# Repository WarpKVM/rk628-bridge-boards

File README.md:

# RK628H HDMI to MIPI CSI-2 bridge boards

Three small boards that turn an HDMI source into a MIPI CSI-2 camera stream,
built around the Rockchip RK628H. We designed them while building
[WarpKVM](https://warpkvm.com), used them to write and measure our capture
pipeline, and they are released here as open hardware so anyone can build on
them.

| | [`rk628-22p`](rk628-22p/) | [`rk628-30p`](rk628-30p/) | [`rk628-2x22p`](rk628-2x22p/) |
|---|---|---|---|
| Host connector | 22-pin FPC, 0.5 mm | 30-pin FPC, 0.5 mm | Two 22-pin FPCs, 0.5 mm |
| CSI-2 link | 4 lanes | 4 lanes | 2 x 4 lanes |
| Best mode | 4K30, 1080p120 | 4K30, 1080p120 | 4K60 (captured on the DIY shield) |
| Audio | I2S header | On-board DAC, 3.5 mm jack | I2S header |
| Size | 45 x 30 mm | 46.25 x 30 mm | 49 x 32.5 mm |
| Tested on | Luckfox Aura (RV1126B), Raspberry Pi CM4, Pi 4B lane count | Firefly ROC-RK3576-PC | Luckfox Aura, via the same circuit on our DIY shield |
| Install | One boot image (Aura) or one script that builds the driver (Pi) | Works on the factory image; one script for the patched kernel | One boot image |
| Status | Built and tested | Built and tested | Not yet fabricated |

The numbers on these pages were measured on real hardware, with the RK628H.
The RK628D also works on the single-link boards and is probably the better pick
for them; each board's README has the details.

## What is in each board folder

- `schematic/`: the schematic as a PDF
- `cad/`: the Fusion archive, plus EAGLE `.sch` and `.brd` files that KiCad can import
- `fab/`: gerbers, drill file, JLCPCB BOM and pick-and-place, and fab notes
  (stackup, impedance, finish)
- `images/`: photos, dimensions, a connection diagram and one image per layer

Host support (drivers, device trees, installers and EDIDs) is in [`hosts/`](hosts/).

## Why these boards

- **Up to 4K30 or 1080p120 on one 4-lane link**, and 4K60 over two
- **Custom EDIDs that apply live**, with no cable replug
- **HDMI audio**, over I2S to the host or to an on-board DAC
- **Automatic recovery** from the bridge lockup a hot HDMI replug can cause

The last three need the driver fixes in [`hosts/`](hosts/). Rockchip's stock
driver drops hot plug after an EDID write, never advertises audio, and caps the
lane rate on chips that do not need it. Each fix is described there.

## Getting started

1. Pick the board that matches your host's camera connector.
2. Start from the host's stock image: Firefly's Ubuntu, Luckfox's Debian or
   Raspberry Pi OS.
3. Connect the bridge with a 0.5 mm pitch FPC cable before powering on.
4. Run the installer for your host from the board's README, then
   `rk628-check.sh`, which finds the bridge, shows what the source is sending
   and captures a few hundred frames.

## Libraries

The Fusion libraries these boards use, with JLCPCB part numbers, schematic
frames and power symbols, are in
[groundplane-studio/fusion-libraries](https://github.com/groundplane-studio/fusion-libraries).

## Disclaimer

These boards and drivers are provided as is, with no warranty of any kind. They are
reference designs we've tested on the hosts listed above, not certified products.
Building, modifying or using them is at your own risk: check the design against your
own requirements, and we're not liable for damage to your hardware, your source devices
or anything else. The full terms are in the license files (CERN-OHL-S-2.0 for hardware,
GPL-2.0 for software).

## Licenses

- Hardware (schematics, layout, gerbers): CERN-OHL-S-2.0, see `LICENSE-HARDWARE`
- Software (kernel patches, drivers, device trees, scripts): GPL-2.0, see
  `LICENSE-SOFTWARE`, matching the Rockchip BSP driver they modify

Build, change and sell these boards under those licenses. WarpKVM is our
trademark, so please don't sell copies under that name; "based on the WarpKVM
RK628 boards" is fine.

## Community

Questions, builds and ports to other hosts are welcome. Join us on
[Discord](https://discord.gg/7eus4CZ4DT).

## About WarpKVM

These boards are where WarpKVM started. The same RK628H capture path, tuned for
latency, is inside the [WarpKVM 01](https://warpkvm.com/01?utm_source=github&utm_medium=readme&utm_campaign=rk628-bridge-boards):
a low-latency IP KVM for remote control that feels local.

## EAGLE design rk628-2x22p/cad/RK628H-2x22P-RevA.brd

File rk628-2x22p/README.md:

# rk628-2x22p: RK628H bridge, dual 22-pin FPC

HDMI in, two 4-lane MIPI CSI-2 links out over two 22-pin 0.5 mm FPCs. Above a
300 MHz pixel clock the RK628H splits each frame left and right across both
links, which is what carries 4K60. The host joins the halves back together.

A render from the Fusion design. Photos follow once the first boards are built.
Gerber renders of the top and bottom are in `images/render-top-store.png` and
`images/render-bottom-store.png`.

## Status

This board has not been fabricated yet. It uses the same circuit and FPC wiring
as our DIY WarpKVM shield for the Luckfox Aura, in a new layout, so the results
below are from the shield. To be tested on the final board.

| Mode | Luckfox Aura, DIY shield |
|---|---|
| 3840x2160 @ 60 | 60.00 fps over 600 frames, 0 errors, halves line up |

Measured on Luckfox's stock Debian 13 image with the `rk628-2x22p` boot image
below. The driver switches to dual link by itself for any mode above 300 MHz
and uses one link below that.

## Luckfox Aura

1. Flash Luckfox's Debian 13 image for the Aura (SD card or eMMC).
2. Power off. Connect **J1 to the Aura's CSI0** and **J6 to CSI1**. J1 carries
   the I2C, reset and interrupt lines, so it must go to CSI0. Connect an HDMI
   source.
3. Power on, download `rk628-aura-boot-6.1.141.tar.gz` from the
   [releases page](https://github.com/WarpKVM/rk628-bridge-boards/releases),
   copy it to the Aura, then:

```bash
tar xf rk628-aura-boot-6.1.141.tar.gz
sudo sh rk628-aura-boot/install.sh rk628-2x22p
```

4. Unplug the Aura and plug it back in (not `reboot`), then:

```bash
sudo sh rk628-aura-boot/rk628-check.sh
```

For 4K60, load [`2160p60.hex`](../hosts/edid/2160p60.hex) with
`sudo v4l2-ctl -d /dev/v4l-subdev3 --set-edid=pad=0,file=2160p60.hex,format=hex`
and set the source to 60 Hz.

## Files

| Path | What |
|---|---|
| `schematic/RK628H-2x22P-RevA-schematic.pdf` | Schematic |
| `cad/` | Fusion archive (`.f3z`) and EAGLE schematic and board (`.sch`, `.brd`), which KiCad can import |
| `fab/gerbers/` | Gerbers and drill file |
| `fab/bom-jlcpcb.csv`, `fab/cpl-jlcpcb.csv` | BOM and pick-and-place in JLCPCB format, plus the not-fitted lists |
| `fab/fab-notes.txt` | Stackup, impedance, finish and drill table |
| `images/` | Renders and one image per layer, made from the gerbers |
| `../hosts/luckfox-aura/dts/` | Dual link device tree for the Aura |

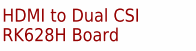
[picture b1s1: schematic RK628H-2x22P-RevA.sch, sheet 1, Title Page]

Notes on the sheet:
HDMI to Dual CSI RK628H Board

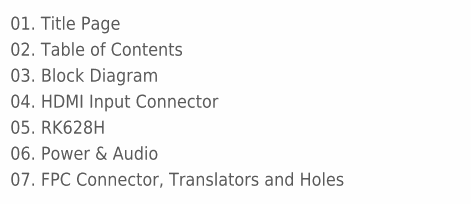
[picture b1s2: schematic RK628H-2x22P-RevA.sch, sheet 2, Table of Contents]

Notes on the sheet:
01. Title Page
02. Table of Contents
03. Block Diagram
04. HDMI Input Connector
06. Power & Audio
07. FPC Connector, Translators and Holes
05. RK628H

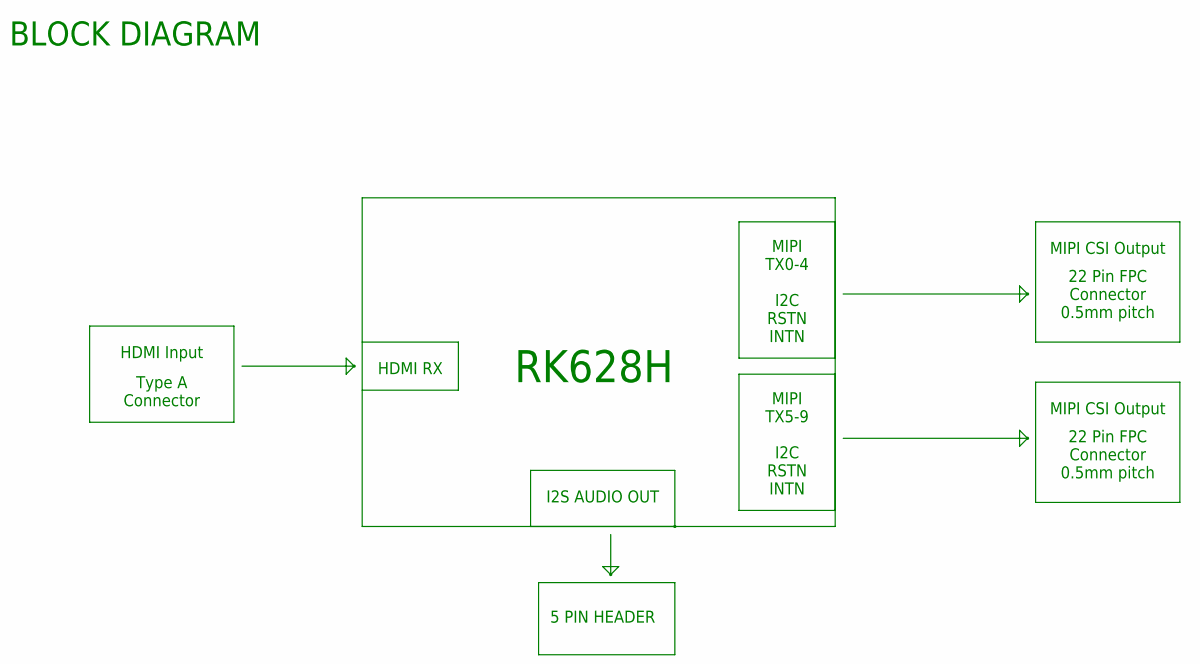
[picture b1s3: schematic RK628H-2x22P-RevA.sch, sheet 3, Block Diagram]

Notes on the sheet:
BLOCK DIAGRAM
HDMI Input
RK628H
Type A Connector
HDMI RX
I2S AUDIO OUT
5 PIN HEADER
MIPI CSI Output
22 Pin FPC Connector 0.5mm pitch
MIPI TX0-4
I2C RSTN INTN
MIPI TX5-9

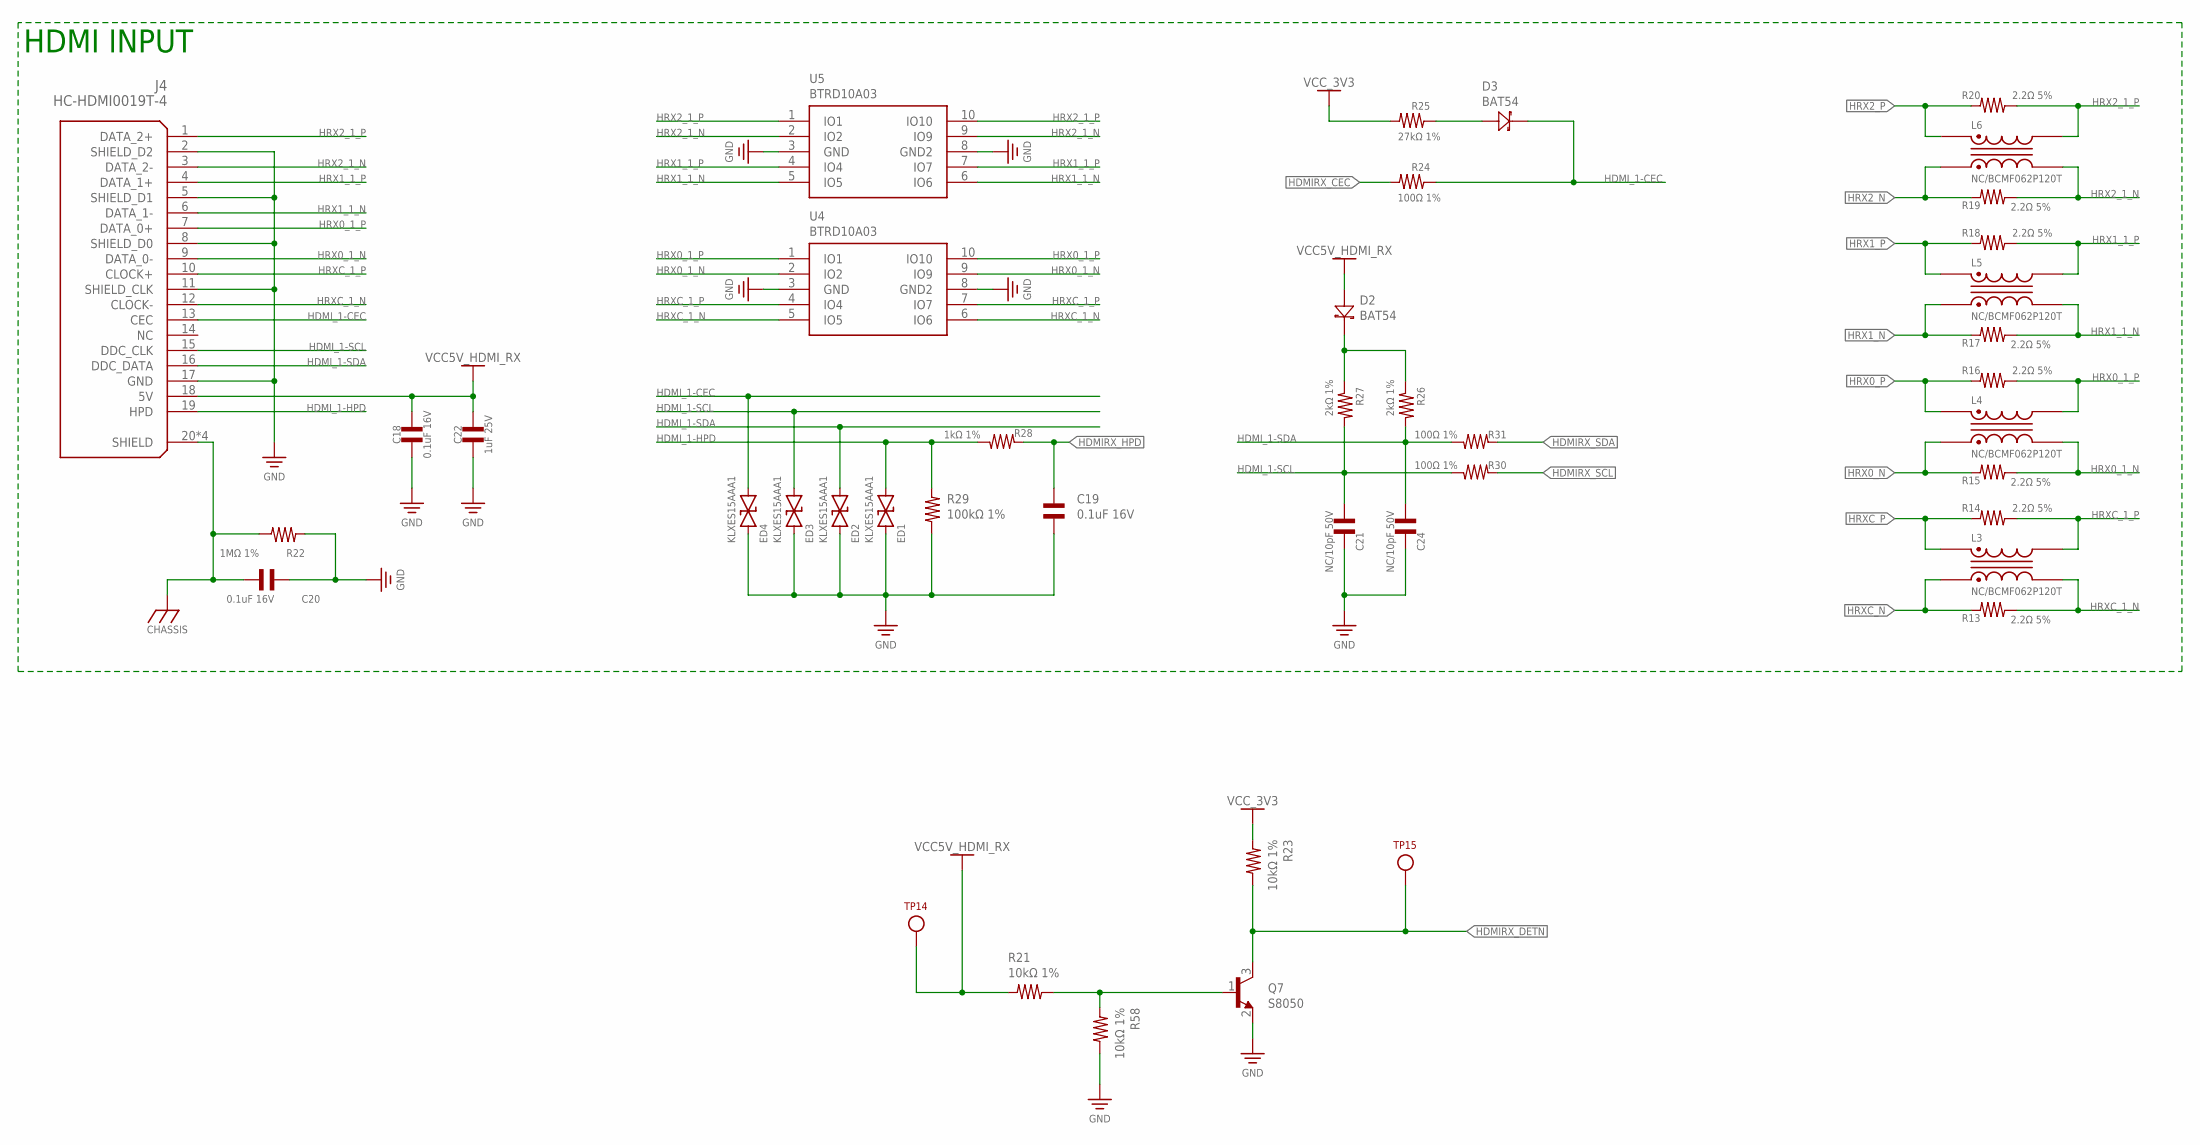
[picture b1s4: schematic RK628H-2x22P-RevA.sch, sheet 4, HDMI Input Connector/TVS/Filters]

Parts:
C18, C19, C20: 0.1uF 16V; CAP_0402
C21, C24: NC/10pF 50V; CAP_0201
C22: 1uF 25V; CAP_0402
D2, D3: BAT54; SOT-23-3
ED1, ED2, ED3, ED4: KLXES15AAA1; TVS_0402
J4: HC-HDMI0019T-4; CONN_HDMI_A_SMT_RA_HC-HDMI0019T-4
L3, L4, L5, L6: NC/BCMF062P120T; BCMF062P120T
Q7: S8050; SOT-23-3
R13, R14, R15, R16, R17, R18, R19, R20: 2.2Ω 5%; RES_0201
R21, R23, R58: 10kΩ 1%; RES_0402
R22: 1MΩ 1%; RES_0402
R24, R30, R31: 100Ω 1%; RES_0402
R25: 27kΩ 1%; RES_0402
R26, R27: 2kΩ 1%; RES_0402
R28: 1kΩ 1%; RES_0402
R29: 100kΩ 1%; RES_0402
TP14, TP15: TEST_POINT_1MM_0.5MM; TEST_POINT_1MM
U4, U5: BTRD10A03; DFN2510-10

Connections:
CGND: C20.2, J4.20 (SHIELD), J4.21 (SHIELD), J4.22 (SHIELD), J4.23 (SHIELD), R22.1; also elsewhere on the board
GND: C18.1, C19.1, C20.1, C21.1, C22.1, C24.1, ED1.1, ED2.1, ED3.1, ED4.1, J4.2 (SHIELD_D2), J4.5 (SHIELD_D1), J4.8 (SHIELD_D0), J4.11 (SHIELD_CLK), J4.17 (GND), Q7.2 (E), R22.2, R29.1, R58.1, U4.3 (GND), U4.8 (GND2), U5.3 (GND), U5.8 (GND2); also elsewhere on the board
HDMIRX_CEC: R24.2; also elsewhere on the board
HDMIRX_DETN: Q7.3 (C), R23.1, TP15.P$1; also elsewhere on the board
HDMIRX_HPD: C19.2, R28.2; also elsewhere on the board
HDMIRX_SCL: R30.2; also elsewhere on the board
HDMIRX_SDA: R31.2; also elsewhere on the board
HDMI_1-CEC: D3.3 (C), ED4.2, J4.13 (CEC), R24.1
HDMI_1-HPD: ED1.2, J4.19 (HPD), R28.1, R29.2
HDMI_1-SCL: C21.2, ED3.2, J4.15 (DDC_CLK), R27.2, R30.1
HDMI_1-SDA: C24.2, ED2.2, J4.16 (DDC_DATA), R26.2, R31.1
HRX0_1_N: J4.9 (DATA_0-), L4.3, R15.1, U4.2 (IO2), U4.9 (IO9)
HRX0_1_P: J4.7 (DATA_0+), L4.4, R16.1, U4.1 (IO1), U4.10 (IO10)
HRX0_N: L4.2, R15.2; also elsewhere on the board
HRX0_P: L4.1, R16.2; also elsewhere on the board
HRX1_1_N: J4.6 (DATA_1-), L5.3, R17.1, U5.5 (IO5), U5.6 (IO6)
HRX1_1_P: J4.4 (DATA_1+), L5.4, R18.1, U5.4 (IO4), U5.7 (IO7)
HRX1_N: L5.2, R17.2; also elsewhere on the board
HRX1_P: L5.1, R18.2; also elsewhere on the board
HRX2_1_N: J4.3 (DATA_2-), L6.3, R19.1, U5.2 (IO2), U5.9 (IO9)
HRX2_1_P: J4.1 (DATA_2+), L6.4, R20.1, U5.1 (IO1), U5.10 (IO10)
HRX2_N: L6.2, R19.2; also elsewhere on the board
HRX2_P: L6.1, R20.2; also elsewhere on the board
HRXC_1_N: J4.12 (CLOCK-), L3.3, R13.1, U4.5 (IO5), U4.6 (IO6)
HRXC_1_P: J4.10 (CLOCK+), L3.4, R14.1, U4.4 (IO4), U4.7 (IO7)
HRXC_N: L3.2, R13.2; also elsewhere on the board
HRXC_P: L3.1, R14.2; also elsewhere on the board
unnamed: D2.3 (C), R26.1, R27.1
unnamed: D3.1 (A), R25.1
unnamed: Q7.1 (B), R21.1, R58.2
VCC5V_HDMI_RX: C18.2, C22.2, D2.1 (A), J4.18 (5V), R21.2, TP14.P$1
VCC_3V3: R23.2, R25.2; also elsewhere on the board

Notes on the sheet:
HDMI INPUT

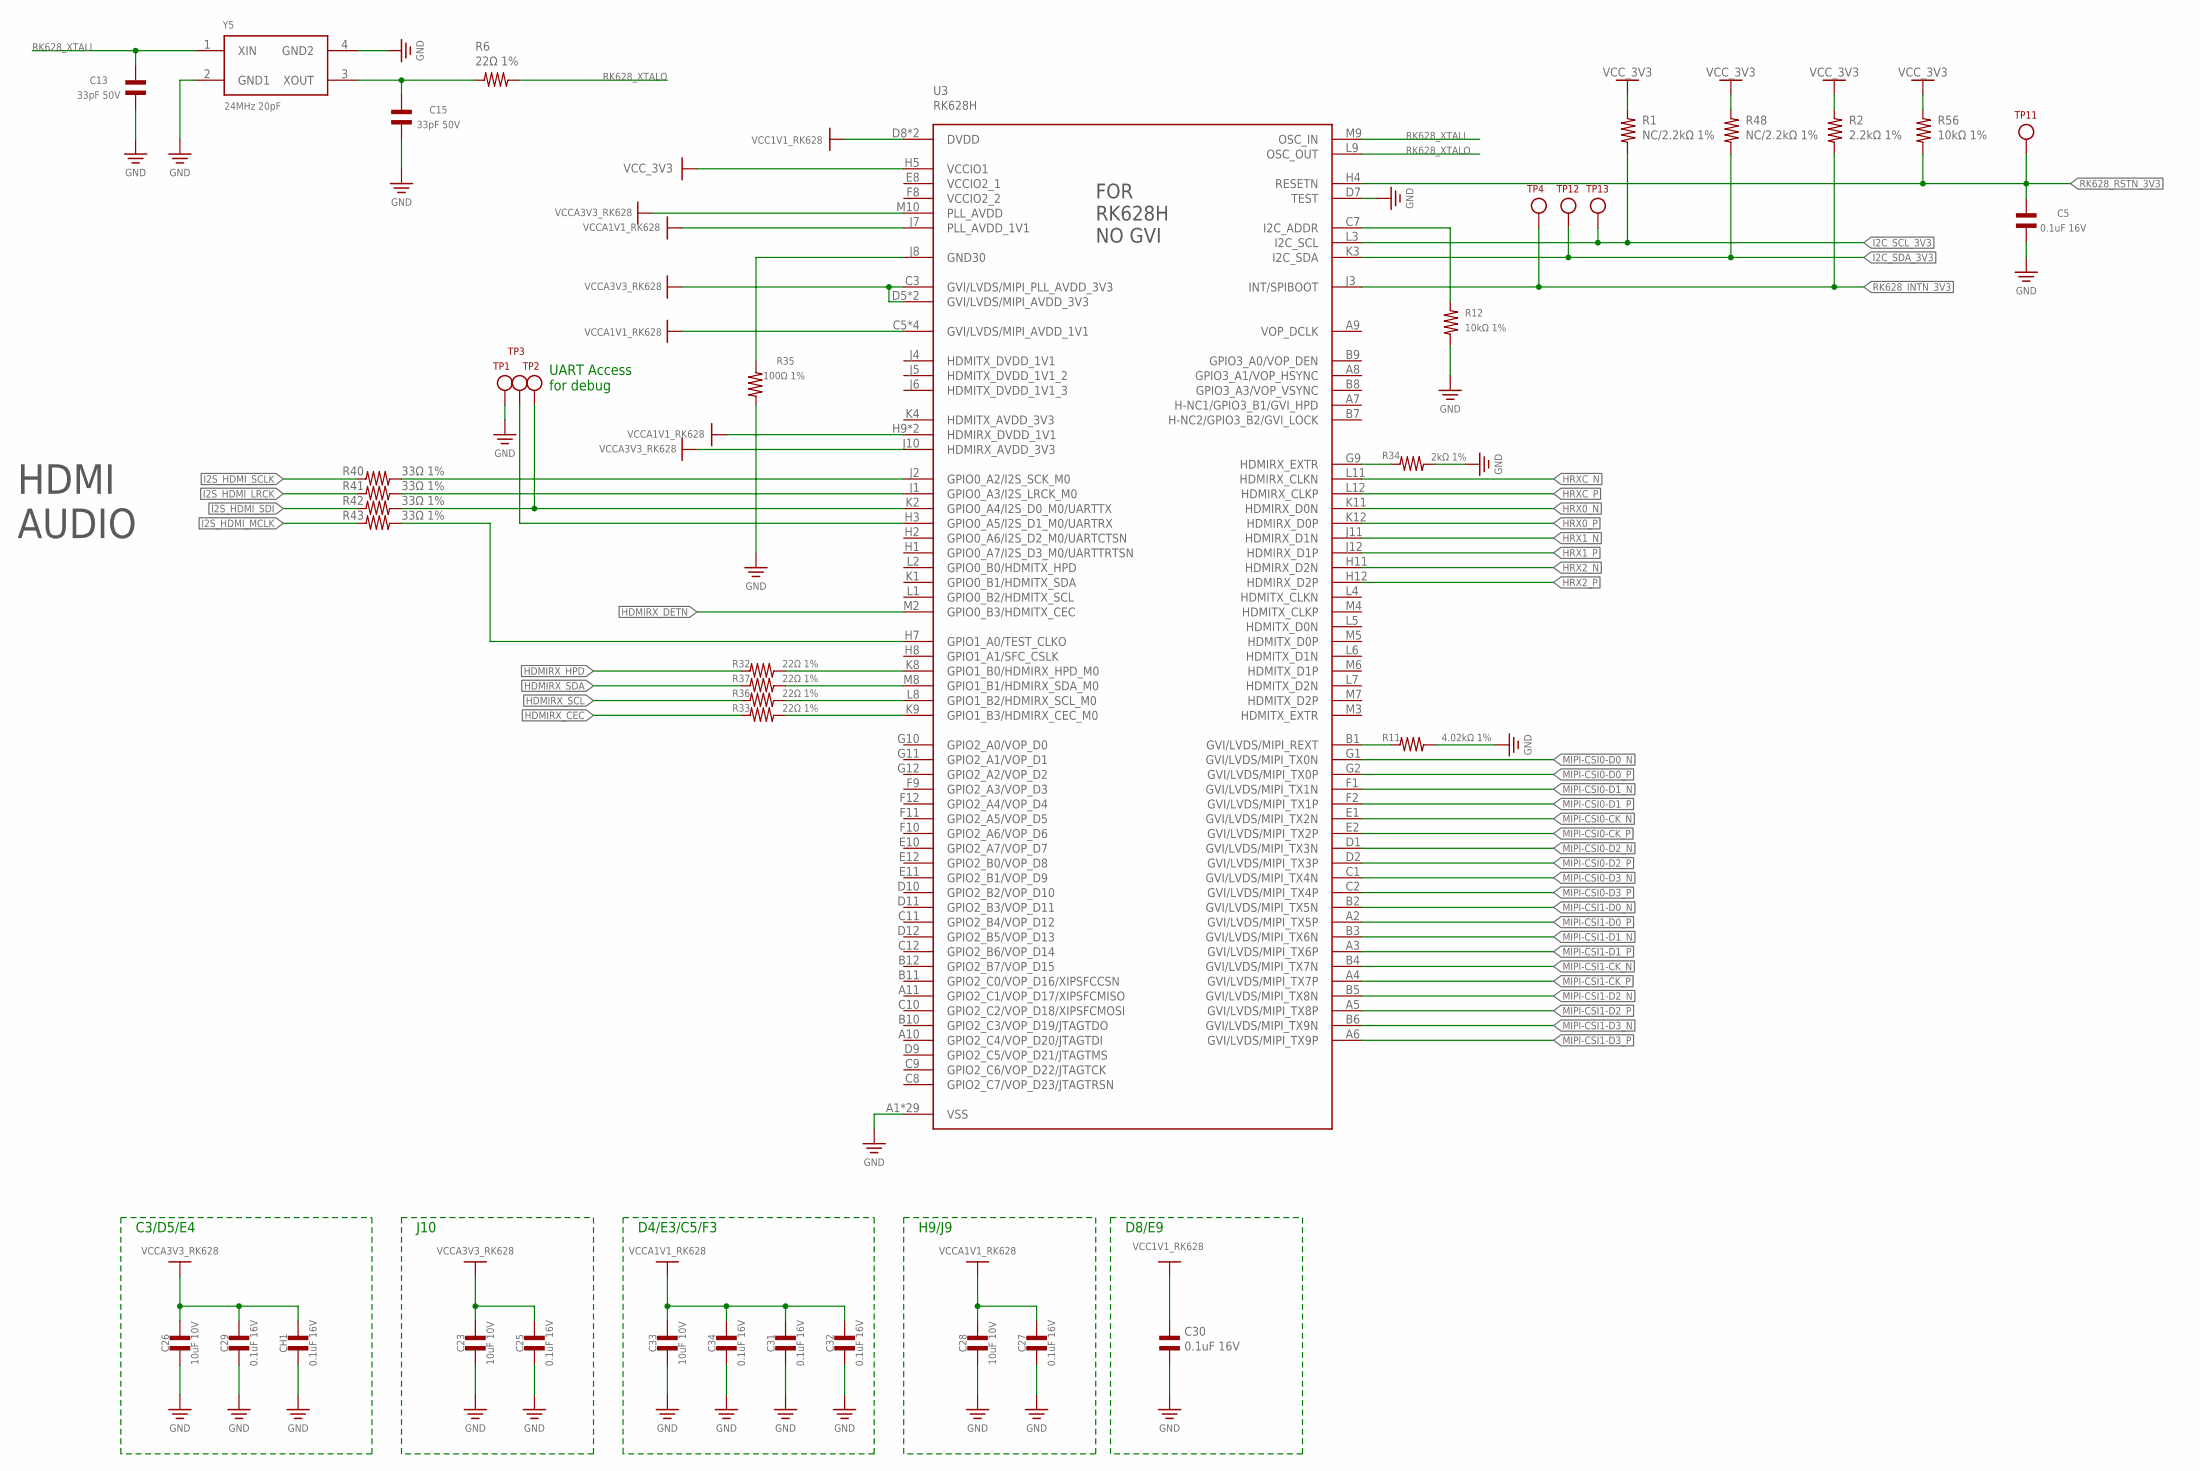
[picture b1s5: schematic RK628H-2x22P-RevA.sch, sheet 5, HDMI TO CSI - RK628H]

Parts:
C5, C25, C27, C29, C30, C31, C32, C34: 0.1uF 16V; CAP_0402
C13, C15: 33pF 50V; CAP_0402
C23, C26, C28, C33: 10uF 10V; CAP_0402
CH1: 0.1uF 16V; CAP_0402
R1, R48: NC/2.2kΩ 1%; RES_0402
R2: 2.2kΩ 1%; RES_0402
R6, R32, R33, R36, R37: 22Ω 1%; RES_0402
R11: 4.02kΩ 1%; RES_0402
R12, R56: 10kΩ 1%; RES_0402
R34: 2kΩ 1%; RES_0402
R35: 100Ω 1%; RES_0402
R40, R41, R42, R43: 33Ω 1%; RES_0402
TP1, TP2, TP3, TP11: TESTPOINT_1MM; TEST_POINT_1MM
TP4, TP12, TP13: TEST_POINT_1MM_0.5MM; TEST_POINT_1MM
U3: RK628H; WBBGA144_8X8MM
Y5: 24MHz 20pF; CRYSTAL_SMD2016-4P

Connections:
GND: C5.1, C13.1, C15.1, C23.1, C25.1, C26.1, C27.1, C28.1, C29.1, C30.2, C31.1, C32.1, C33.1, C34.1, CH1.1, R11.1, R12.1, R34.1, R35.2, TP1.P$1, U3.A1 (VSS), U3.A12 (VSS), U3.C4 (VSS), U3.C6 (VSS), U3.D3 (VSS), U3.D6 (VSS), U3.D7 (TEST), U3.E5 (VSS), U3.E6 (VSS), U3.E7 (VSS), U3.F4 (VSS), U3.F5 (VSS), U3.F6 (VSS), U3.F7 (VSS), U3.G3 (VSS), U3.G4 (VSS), U3.G5 (VSS), U3.G6 (VSS), U3.G7 (VSS), U3.G8 (VSS), U3.H6 (VSS), U3.H10 (VSS), U3.K5 (VSS), U3.K6 (VSS), U3.K7 (VSS), U3.K10 (VSS), U3.L10 (VSS), U3.M1 (VSS), U3.M11 (VSS), U3.M12 (VSS), Y5.2 (GND1), Y5.4 (GND2); also elsewhere on the board
HDMIRX_CEC: R33.2; also elsewhere on the board
HDMIRX_DETN: U3.M2 (GPIO0_B3/HDMITX_CEC); also elsewhere on the board
HDMIRX_HPD: R32.2; also elsewhere on the board
HDMIRX_SCL: R36.2; also elsewhere on the board
HDMIRX_SDA: R37.2; also elsewhere on the board
HDMITX_AVDD_3V3: U3.K4 (HDMITX_AVDD_3V3)
HDMITX_DVDD_1V1: U3.J4 (HDMITX_DVDD_1V1)
HDMITX_DVDD_1V1_2: U3.J5 (HDMITX_DVDD_1V1_2)
HDMITX_DVDD_1V1_3: U3.J6 (HDMITX_DVDD_1V1_3)
HRX0_N: U3.K11 (HDMIRX_D0N); also elsewhere on the board
HRX0_P: U3.K12 (HDMIRX_D0P); also elsewhere on the board
HRX1_N: U3.J11 (HDMIRX_D1N); also elsewhere on the board
HRX1_P: U3.J12 (HDMIRX_D1P); also elsewhere on the board
HRX2_N: U3.H11 (HDMIRX_D2N); also elsewhere on the board
HRX2_P: U3.H12 (HDMIRX_D2P); also elsewhere on the board
HRXC_N: U3.L11 (HDMIRX_CLKN); also elsewhere on the board
HRXC_P: U3.L12 (HDMIRX_CLKP); also elsewhere on the board
I2C_SCL_3V3: R1.1, TP13.P$1, U3.L3 (I2C_SCL); also elsewhere on the board
I2C_SDA_3V3: R48.1, TP12.P$1, U3.K3 (I2C_SDA); also elsewhere on the board
I2S_HDMI_LRCK: R41.2; also elsewhere on the board
I2S_HDMI_MCLK: R43.2; also elsewhere on the board
I2S_HDMI_SCLK: R40.2; also elsewhere on the board
I2S_HDMI_SDI: R42.2; also elsewhere on the board
MIPI-CSI0-CK_N: U3.E1 (GVI/LVDS/MIPI_TX2N); also elsewhere on the board
MIPI-CSI0-CK_P: U3.E2 (GVI/LVDS/MIPI_TX2P); also elsewhere on the board
MIPI-CSI0-D0_N: U3.G1 (GVI/LVDS/MIPI_TX0N); also elsewhere on the board
MIPI-CSI0-D0_P: U3.G2 (GVI/LVDS/MIPI_TX0P); also elsewhere on the board
MIPI-CSI0-D1_N: U3.F1 (GVI/LVDS/MIPI_TX1N); also elsewhere on the board
MIPI-CSI0-D1_P: U3.F2 (GVI/LVDS/MIPI_TX1P); also elsewhere on the board
MIPI-CSI0-D2_N: U3.D1 (GVI/LVDS/MIPI_TX3N); also elsewhere on the board
MIPI-CSI0-D2_P: U3.D2 (GVI/LVDS/MIPI_TX3P); also elsewhere on the board
MIPI-CSI0-D3_N: U3.C1 (GVI/LVDS/MIPI_TX4N); also elsewhere on the board
MIPI-CSI0-D3_P: U3.C2 (GVI/LVDS/MIPI_TX4P); also elsewhere on the board
MIPI-CSI1-CK_N: U3.B4 (GVI/LVDS/MIPI_TX7N); also elsewhere on the board
MIPI-CSI1-CK_P: U3.A4 (GVI/LVDS/MIPI_TX7P); also elsewhere on the board
MIPI-CSI1-D0_N: U3.B2 (GVI/LVDS/MIPI_TX5N); also elsewhere on the board
MIPI-CSI1-D0_P: U3.A2 (GVI/LVDS/MIPI_TX5P); also elsewhere on the board
MIPI-CSI1-D1_N: U3.B3 (GVI/LVDS/MIPI_TX6N); also elsewhere on the board
MIPI-CSI1-D1_P: U3.A3 (GVI/LVDS/MIPI_TX6P); also elsewhere on the board
MIPI-CSI1-D2_N: U3.B5 (GVI/LVDS/MIPI_TX8N); also elsewhere on the board
MIPI-CSI1-D2_P: U3.A5 (GVI/LVDS/MIPI_TX8P); also elsewhere on the board
MIPI-CSI1-D3_N: U3.B6 (GVI/LVDS/MIPI_TX9N); also elsewhere on the board
MIPI-CSI1-D3_P: U3.A6 (GVI/LVDS/MIPI_TX9P); also elsewhere on the board
unnamed: C15.2, R6.2, Y5.3 (XOUT)
unnamed: R40.1, U3.J2 (GPIO0_A2/I2S_SCK_M0)
unnamed: R41.1, U3.J1 (GPIO0_A3/I2S_LRCK_M0)
unnamed: R42.1, TP2.P$1, U3.K2 (GPIO0_A4/I2S_D0_M0/UARTTX)
unnamed: R43.1, U3.H7 (GPIO1_A0/TEST_CLKO)
unnamed: R11.2, U3.B1 (GVI/LVDS/MIPI_REXT)
unnamed: R34.2, U3.G9 (HDMIRX_EXTR)
unnamed: R32.1, U3.K8 (GPIO1_B0/HDMIRX_HPD_M0)
unnamed: R37.1, U3.M8 (GPIO1_B1/HDMIRX_SDA_M0)
unnamed: R36.1, U3.L8 (GPIO1_B2/HDMIRX_SCL_M0)
unnamed: R33.1, U3.K9 (GPIO1_B3/HDMIRX_CEC_M0)
unnamed: R35.1, U3.J8 (GND30)
unnamed: TP3.P$1, U3.H3 (GPIO0_A5/I2S_D1_M0/UARTRX)
unnamed: R12.2, U3.C7 (I2C_ADDR)
RK628_INTN_3V3: R2.1, TP4.P$1, U3.J3 (INT/SPIBOOT); also elsewhere on the board
RK628_RSTN_3V3: C5.2, R56.1, TP11.P$1, U3.H4 (RESETN); also elsewhere on the board
RK628_XTALI: C13.2, U3.M9 (OSC_IN), Y5.1 (XIN)
RK628_XTALO: R6.1, U3.L9 (OSC_OUT)
VCC1V1_RK628: C30.1, U3.D8 (DVDD), U3.E9 (DVDD); also elsewhere on the board
VCCA1V1_RK628: C27.2, C28.2, C31.2, C32.2, C33.2, C34.2, U3.C5 (GVI/LVDS/MIPI_AVDD_1V1), U3.D4 (GVI/LVDS/MIPI_AVDD_1V1), U3.E3 (GVI/LVDS/MIPI_AVDD_1V1), U3.F3 (GVI/LVDS/MIPI_AVDD_1V1), U3.H9 (HDMIRX_DVDD_1V1), U3.J7 (PLL_AVDD_1V1), U3.J9 (HDMIRX_DVDD_1V1); also elsewhere on the board
VCCA3V3_RK628: C23.2, C25.2, C26.2, C29.2, CH1.2, U3.C3 (GVI/LVDS/MIPI_PLL_AVDD_3V3), U3.D5 (GVI/LVDS/MIPI_AVDD_3V3), U3.E4 (GVI/LVDS/MIPI_AVDD_3V3), U3.J10 (HDMIRX_AVDD_3V3), U3.M10 (PLL_AVDD); also elsewhere on the board
VCCIO2_1: U3.E8 (VCCIO2_1)
VCCIO2_2: U3.F8 (VCCIO2_2)
VCC_3V3: R1.2, R2.2, R48.2, R56.2, U3.H5 (VCCIO1); also elsewhere on the board

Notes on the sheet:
J10
C3/D5/E4
D4/E3/C5/F3
H9/J9
UART Access for debug
HDMI AUDIO
D8/E9

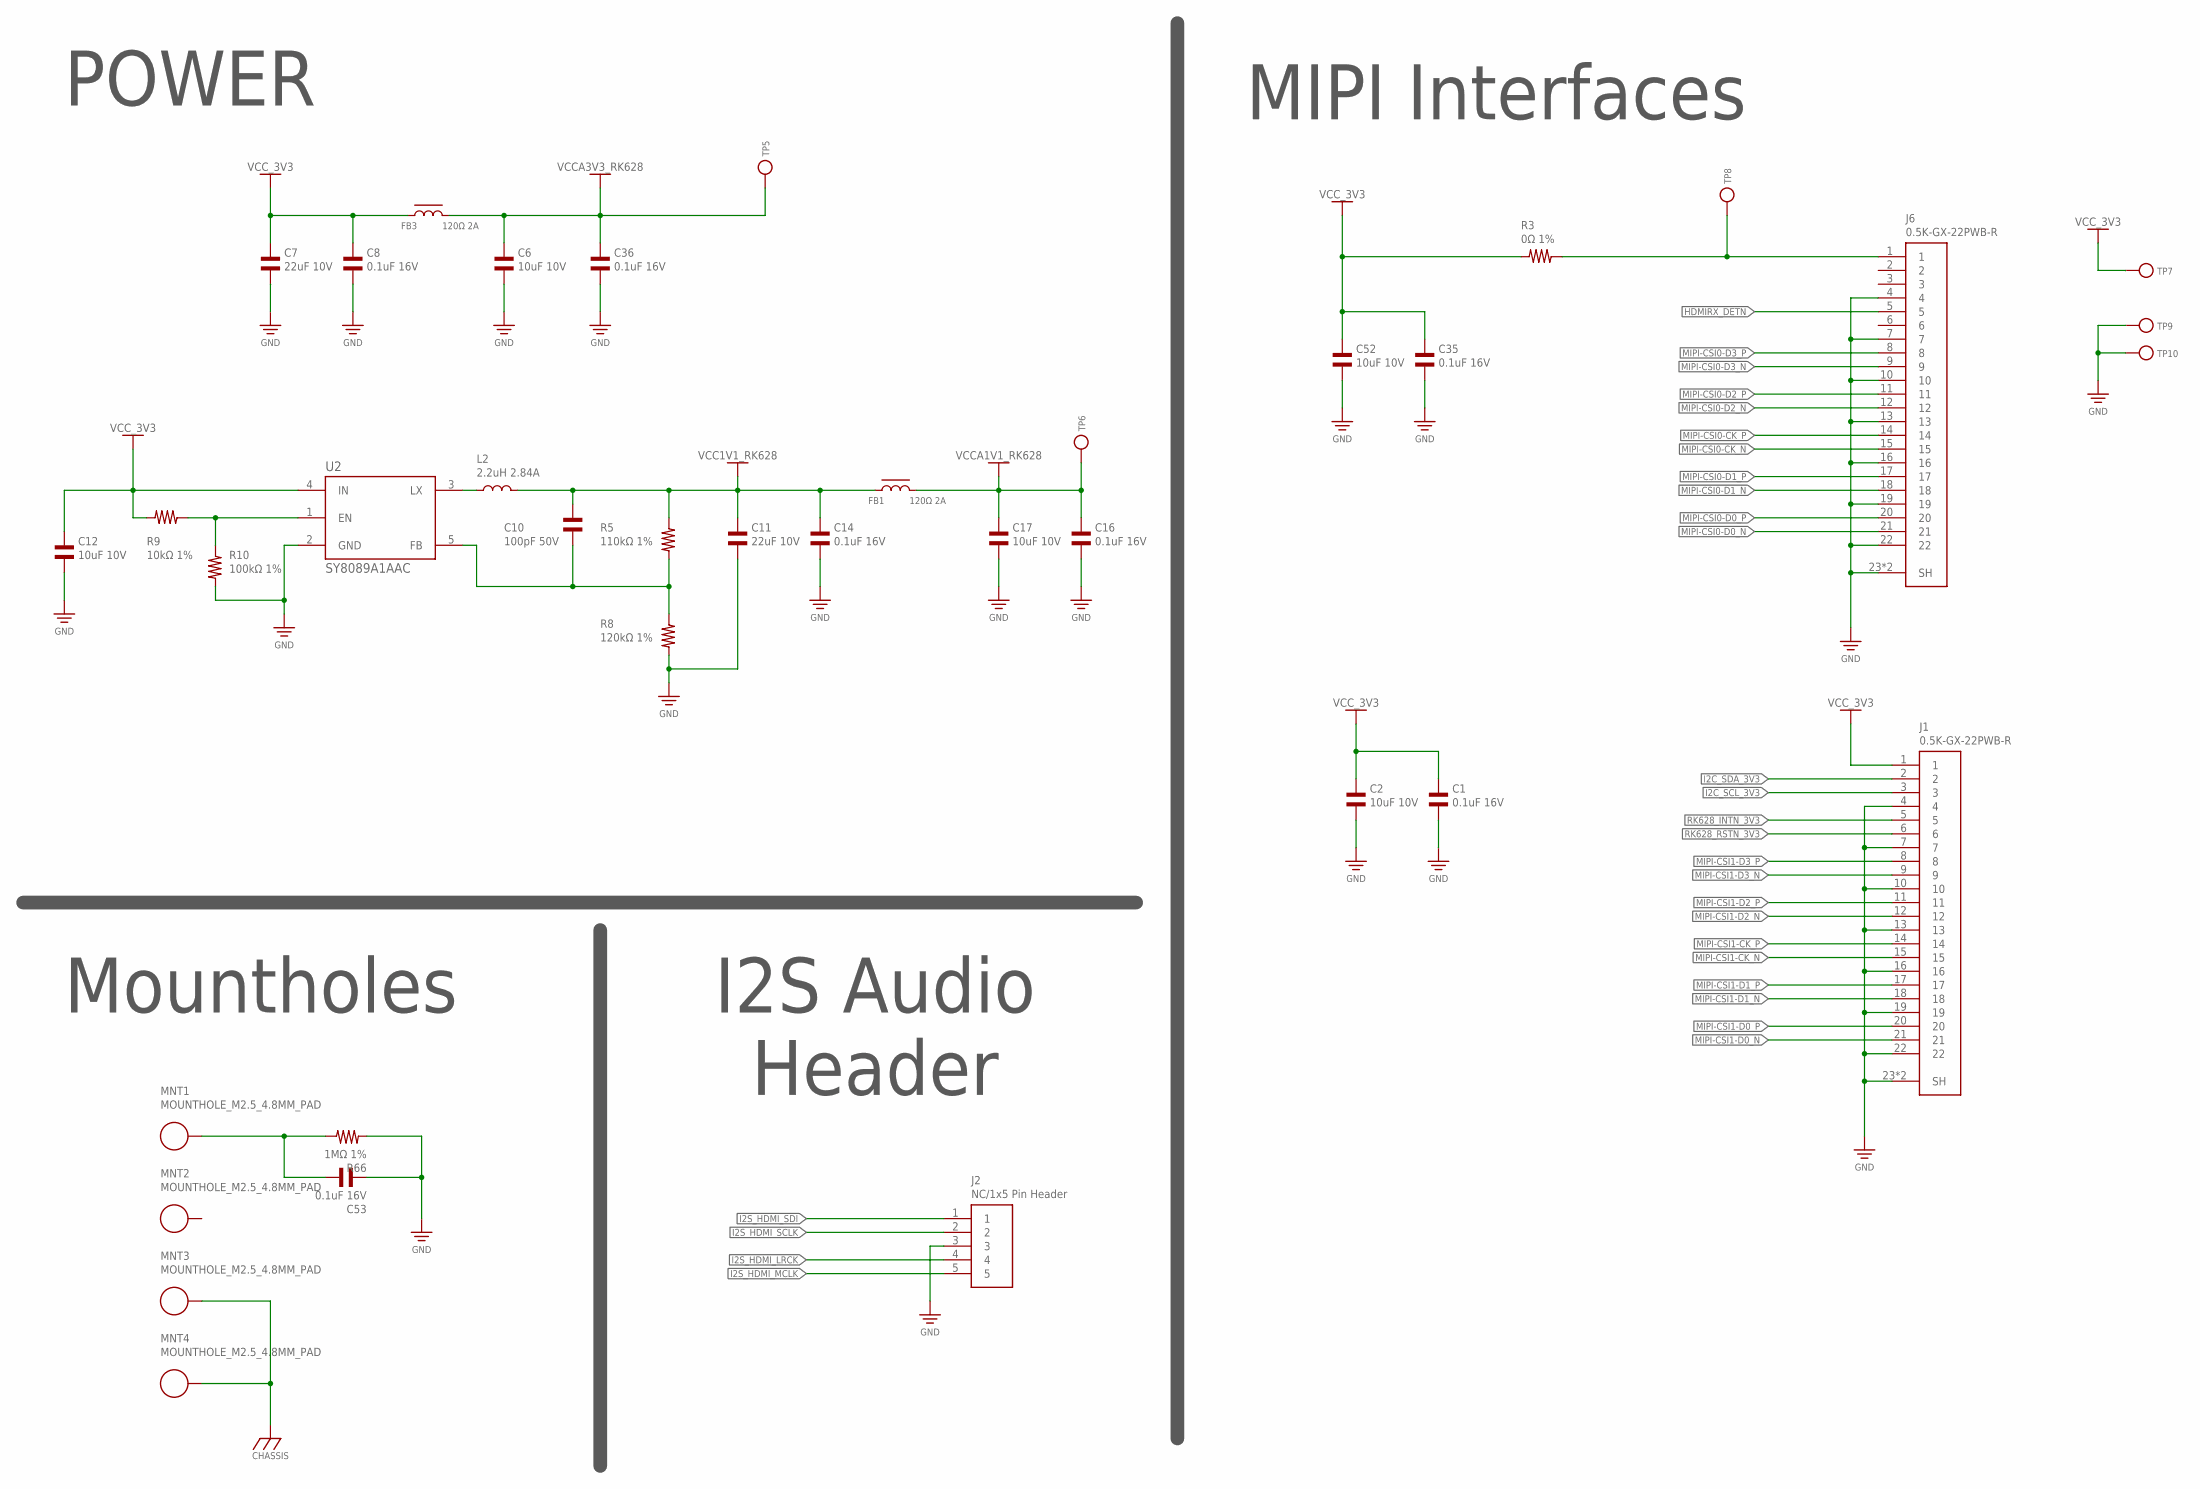
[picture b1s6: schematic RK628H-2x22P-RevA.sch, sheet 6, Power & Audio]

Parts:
C1, C8, C14, C16, C35, C36, C53: 0.1uF 16V; CAP_0402
C2, C6, C12, C17, C52: 10uF 10V; CAP_0402
C7, C11: 22uF 10V; CAP_0603
C10: 100pF 50V; CAP_0402
FB1, FB3: 120Ω 2A; IND_0603
J1, J6: 0.5K-GX-22PWB-R; CONN_FFC_1X22_0.5MM_SM_RA_0.5K-GX-22PWB-R
J2: NC/1x5 Pin Header; HDR_1X05_2.54MM_TH_ST
L2: 2.2uH 2.84A; IND_3MM_SQ_1.2MM_HEIGHT
MNT1, MNT2, MNT3, MNT4: MOUNTHOLE_M2.5_4.8MM_PAD
R3: 0Ω 1%; RES_0402
R5: 110kΩ 1%; RES_0402
R8: 120kΩ 1%; RES_0402
R9: 10kΩ 1%; RES_0402
R10: 100kΩ 1%; RES_0402
R66: 1MΩ 1%; RES_0402
TP5, TP6, TP7, TP8, TP9, TP10: TESTPOINT_1MM; TEST_POINT_1MM
U2: SY8089A1AAC; SOT95P285X110-5N

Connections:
CGND: MNT3.P$1, MNT4.P$1; also elsewhere on the board
GND: C1.2, C2.2, C6.1, C7.1, C8.1, C11.1, C12.1, C14.1, C16.1, C17.1, C35.2, C36.1, C52.2, C53.1, J1.4, J1.7, J1.10, J1.13, J1.16, J1.19, J1.22, J1.23 (SH), J1.24 (SH), J2.3, J6.4, J6.7, J6.10, J6.13, J6.16, J6.19, J6.22, J6.23 (SH), J6.24 (SH), R8.2, R10.2, R66.2, TP9.P$1, TP10.P$1, U2.2 (GND); also elsewhere on the board
HDMIRX_DETN: J6.5; also elsewhere on the board
I2C_SCL_3V3: J1.3; also elsewhere on the board
I2C_SDA_3V3: J1.2; also elsewhere on the board
I2S_HDMI_LRCK: J2.4; also elsewhere on the board
I2S_HDMI_MCLK: J2.5; also elsewhere on the board
I2S_HDMI_SCLK: J2.2; also elsewhere on the board
I2S_HDMI_SDI: J2.1; also elsewhere on the board
MIPI-CSI0-CK_N: J6.15; also elsewhere on the board
MIPI-CSI0-CK_P: J6.14; also elsewhere on the board
MIPI-CSI0-D0_N: J6.21; also elsewhere on the board
MIPI-CSI0-D0_P: J6.20; also elsewhere on the board
MIPI-CSI0-D1_N: J6.18; also elsewhere on the board
MIPI-CSI0-D1_P: J6.17; also elsewhere on the board
MIPI-CSI0-D2_N: J6.12; also elsewhere on the board
MIPI-CSI0-D2_P: J6.11; also elsewhere on the board
MIPI-CSI0-D3_N: J6.9; also elsewhere on the board
MIPI-CSI0-D3_P: J6.8; also elsewhere on the board
MIPI-CSI1-CK_N: J1.15; also elsewhere on the board
MIPI-CSI1-CK_P: J1.14; also elsewhere on the board
MIPI-CSI1-D0_N: J1.21; also elsewhere on the board
MIPI-CSI1-D0_P: J1.20; also elsewhere on the board
MIPI-CSI1-D1_N: J1.18; also elsewhere on the board
MIPI-CSI1-D1_P: J1.17; also elsewhere on the board
MIPI-CSI1-D2_N: J1.12; also elsewhere on the board
MIPI-CSI1-D2_P: J1.11; also elsewhere on the board
MIPI-CSI1-D3_N: J1.9; also elsewhere on the board
MIPI-CSI1-D3_P: J1.8; also elsewhere on the board
unnamed: J6.1, R3.1, TP8.P$1
unnamed: L2.1, U2.3 (LX)
unnamed: C53.2, MNT1.P$1, R66.1
unnamed: C10.1, R5.2, R8.1, U2.5 (FB)
unnamed: R9.1, R10.1, U2.1 (EN)
RK628_INTN_3V3: J1.5; also elsewhere on the board
RK628_RSTN_3V3: J1.6; also elsewhere on the board
VCC1V1_RK628: C10.2, C11.2, C14.2, FB1.1, L2.2, R5.1; also elsewhere on the board
VCCA1V1_RK628: C16.2, C17.2, FB1.2, TP6.P$1; also elsewhere on the board
VCCA3V3_RK628: C6.2, C36.2, FB3.2, TP5.P$1; also elsewhere on the board
VCC_3V3: C1.1, C2.1, C7.2, C8.2, C12.2, C35.1, C52.1, FB3.1, J1.1, R3.2, R9.2, TP7.P$1, U2.4 (IN); also elsewhere on the board

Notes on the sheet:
I2S Audio Header
POWER
MIPI Interfaces
Mountholes

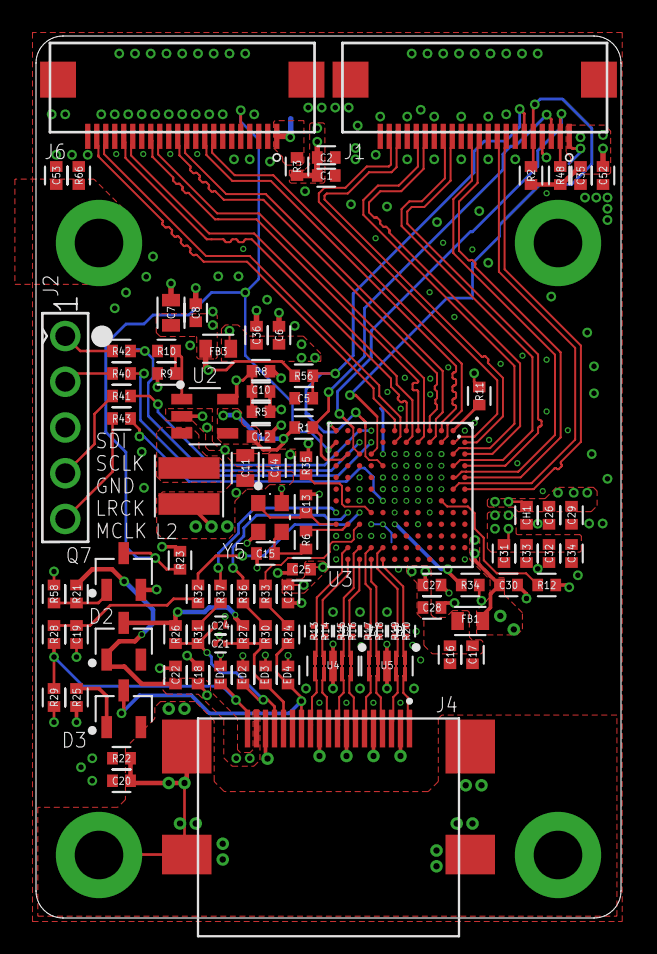
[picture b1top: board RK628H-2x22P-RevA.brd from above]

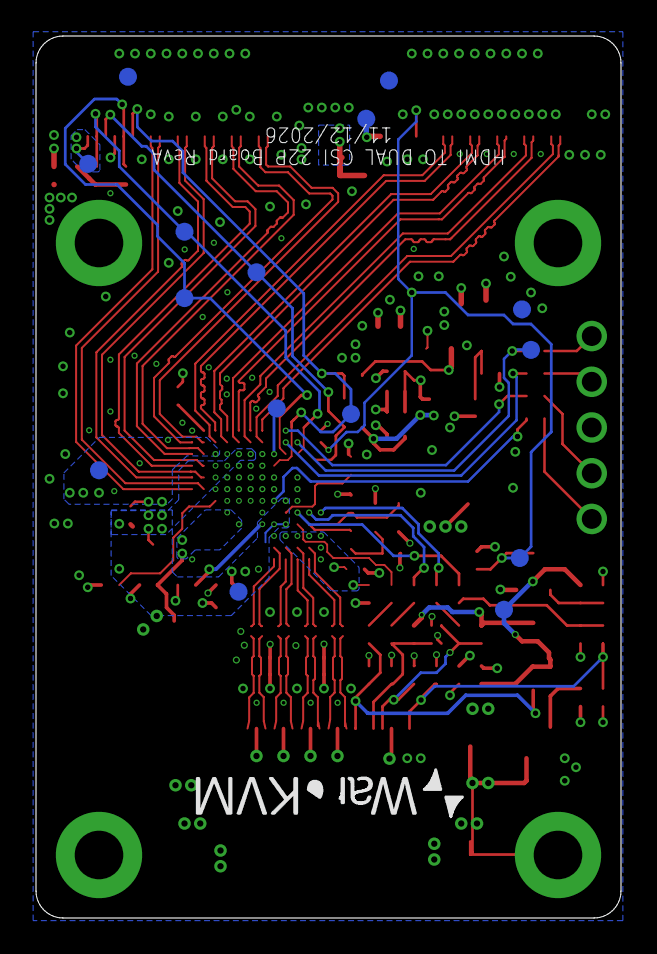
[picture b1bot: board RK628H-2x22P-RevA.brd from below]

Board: 4 copper layers, 32.5 x 49.0 mm, 121 parts (15 on the bottom side), 84 nets.

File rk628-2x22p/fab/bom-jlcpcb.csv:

QTY,Comment,Designator,Footprint,JLCPCB Part #(optional),MF,MP,EQUIV_OK
19,"0.1uF 16V","C1, C5, C8, C14, C16, C18, C19, C20, C25, C27, C29, C30, C31, C32, C34, C35, C36, C53, CH1",CAP_0402,C1525,Samsung Electro-Mechanics,CL05B104KO5NNNC,
9,"10uF 10V","C2, C6, C12, C17, C23, C26, C28, C33, C52",CAP_0402,C315248,Samsung Electro-Mechanics,CL05A106MP5NUNC,
2,"22uF 10V","C7, C11",CAP_0603,C7432770,Chinocera,HGC0603R5226M100NTHJ,
1,"100pF 50V",C10,CAP_0402,C106200,YAGEO,CC0402JRNPO9BN101,
2,"33pF 50V","C13, C15",CAP_0402,C1562,FH (Guangdong Fenghua Advanced Tech),0402CG330J500NT,
1,"1uF 25V",C22,CAP_0402,C52923,Samsung Electro-Mechanics,CL05A105KA5NQNC,
2,"BAT54","D2, D3",SOT-23-3,C8590,,,
4,"KLXES15AAA1","ED1, ED2, ED3, ED4",TVS_0402,C2892490,KUU,KLXES15AAA1,
2,"120Ω 2A","FB1, FB3",IND_0603,C14709,Murata Electronics,BLM18PG121SN1D,
2,"0.5K-GX-22PWB-R","J1, J6",CONN_FFC_1X22_0.5MM_SM_RA_0.5K-GX-22PWB-R,C53223210,GUOCONN,0.5K-GX-22PWB-R,
1,"HC-HDMI0019T-4",J4,CONN_HDMI_A_SMT_RA_HC-HDMI0019T-4,C7501811,Hong Cheng,HC-HDMI0019T-4,
1,"2.2uH 2.84A",L2,IND_3MM_SQ_1.2MM_HEIGHT,C404494,TDK,VLS3012HBX-2R2M,
1,"S8050",Q7,SOT-23-3,C2146,"Jiangsu Changjing Electronics Technology Co., Ltd.",S8050 J3Y(RANGE:200-350),
1,"2.2kΩ 1%",R2,RES_0402,C25879,UNI-ROYAL(Uniroyal Elec),0402WGF2201TCE,
1,"0Ω 1%",R3,RES_0402,C17168,UNI-ROYAL(Uniroyal Elec),0402WGF0000TCE,
1,"110kΩ 1%",R5,RES_0402,C2909311,FOJAN,FRC0402F1103TS,
5,"22Ω 1%","R6, R32, R33, R36, R37",RES_0402,C25092,UNI-ROYAL(Uniroyal Elec),0402WGF220JTCE,
1,"120kΩ 1%",R8,RES_0402,C2909314,FOJAN,FRC0402F1203TS,
6,"10kΩ 1%","R9, R12, R21, R23, R56, R58",RES_0402,C2906861,FOJAN,FRC0402F1002TS,
2,"100kΩ 1%","R10, R29",RES_0402,C25741,UNI-ROYAL(Uniroyal Elec),0402WGF1003TCE,
1,"4.02kΩ 1%",R11,RES_0402,C324800,FH (Guangdong Fenghua Advanced Tech),RC-02K4021FT,
8,"2.2Ω 5%","R13, R14, R15, R16, R17, R18, R19, R20",RES_0201,C270323,UNI-ROYAL(Uniroyal Elec),0201WMJ022JTEE,
2,"1MΩ 1%","R22, R66",RES_0402,C26083,UNI-ROYAL(Uniroyal Elec),0402WGF1004TCE,
4,"100Ω 1%","R24, R30, R31, R35",RES_0402,C25076,UNI-ROYAL(Uniroyal Elec),0402WGF1000TCE,
1,"27kΩ 1%",R25,RES_0402,C138022,YAGEO,RC0402FR-0727KL,
3,"2kΩ 1%","R26, R27, R34",RES_0402,C4109,UNI-ROYAL(Uniroyal Elec),0402WGF2001TCE,
1,"1kΩ 1%",R28,RES_0402,C106235,YAGEO,RC0402FR-071KL,
4,"33Ω 1%","R40, R41, R42, R43",RES_0402,C25105,UNI-ROYAL(Uniroyal Elec),0402WGF330JTCE,
1,"SY8089A1AAC",U2,SOT95P285X110-5N,C479074,Silergy Corp,SY8089A1AAC,
1,"RK628H",U3,WBBGA144_8X8MM,C45369093,Rockchip,RK628H,
2,"BTRD10A03","U4, U5",DFN2510-10,C42375217,KUU,BTRD10A03,
1,"24MHz 20pF",Y5,CRYSTAL_SMD2016-4P,C20885025,Yajingxin,T201624MLBDE2X,
